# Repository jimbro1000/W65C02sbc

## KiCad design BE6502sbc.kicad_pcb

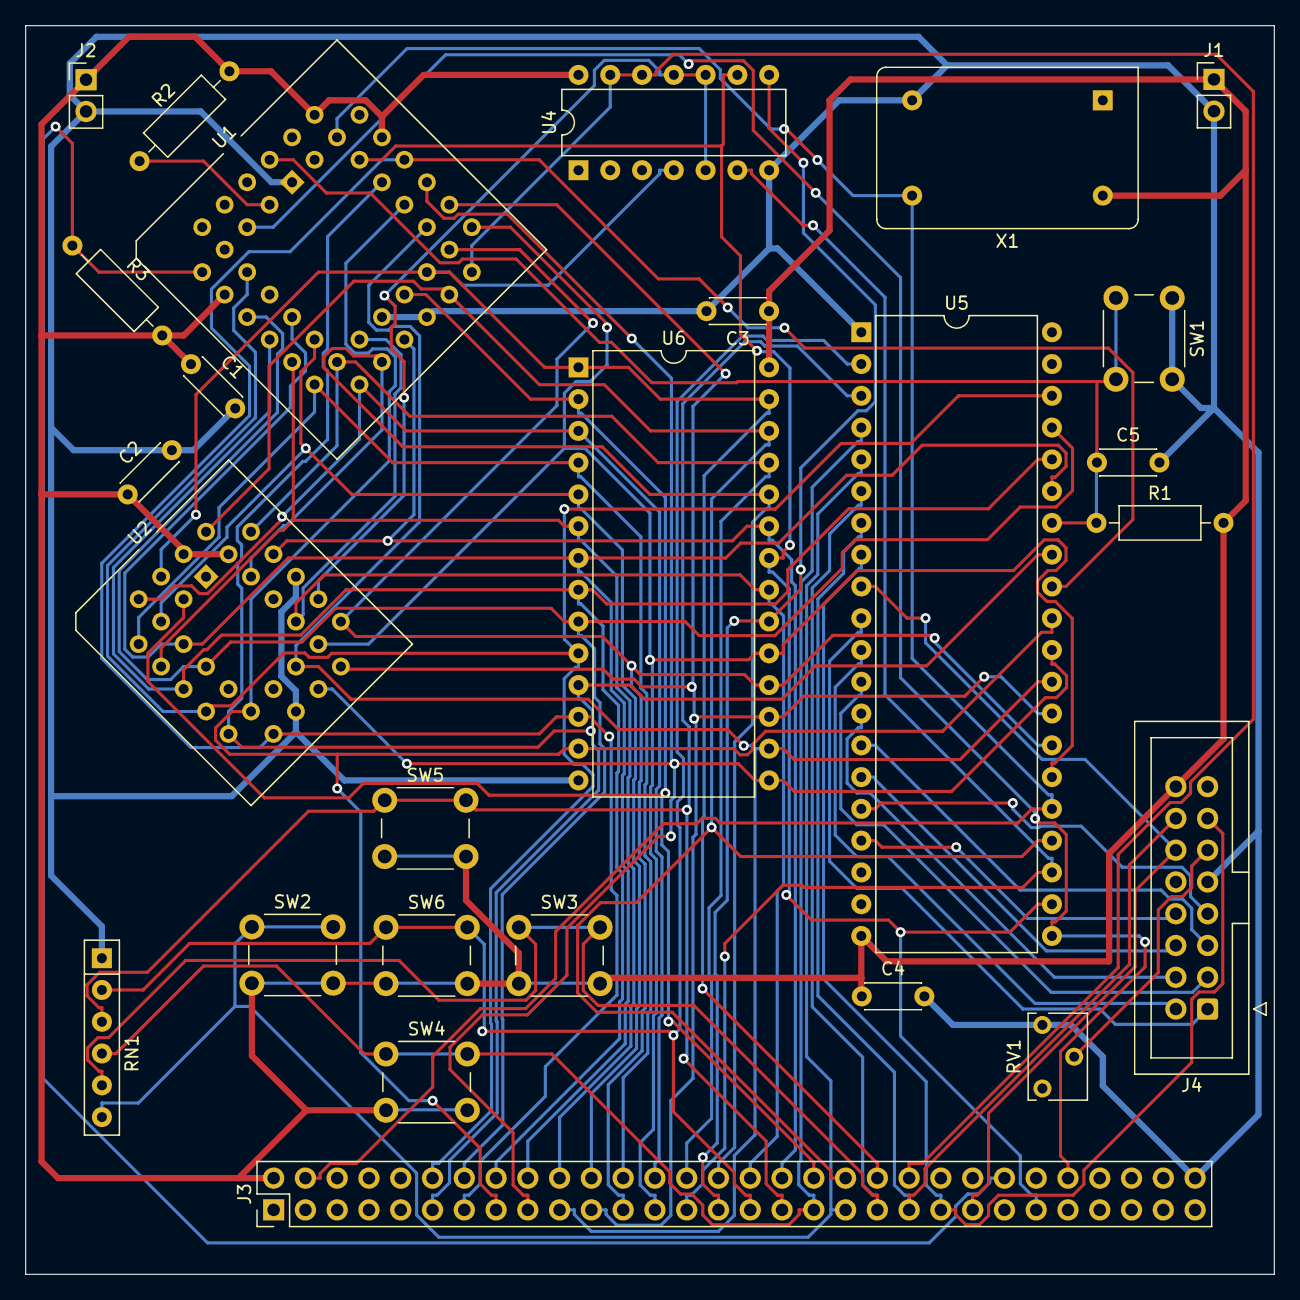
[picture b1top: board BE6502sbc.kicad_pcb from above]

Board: 2 copper layers, 99.8 x 99.8 mm, 26 parts (0 on the bottom side), 52 nets.

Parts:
C1, C2, C3, C4, C5: 100nF; C_Disc_D4.3mm_W1.9mm_P5.00mm
J1, J2: power; PinHeader_1x02_P2.54mm_Vertical
J3: Conn_02x30_Odd_Even; PinHeader_2x30_P2.54mm_Vertical
J4: LCD_DISPLAY; IDC-Header_2x08_P2.54mm_Vertical
R1, R2, R3: 1K; R_Axial_DIN0207_L6.3mm_D2.5mm_P10.16mm_Horizontal
RN1: 1K; R_Array_SIP6
RV1: 10K; Potentiometer_Bourns_3266W_Vertical
SW1: RESET; SW_PUSH_6mm
SW2: LEFT; SW_PUSH_6mm
SW3: RIGHT; SW_PUSH_6mm
SW4: DOWN; SW_PUSH_6mm
SW5: UP; SW_PUSH_6mm
SW6: SELECT; SW_PUSH_6mm
U1: W65C02; PLCC-44_THT-Socket
U2: 28C256; PLCC-32_THT-Socket
U4: 74HC00; DIP-14_W7.62mm
U5: 6522; DIP-40_W15.24mm
U6: KM62256CLP; DIP-28_W15.24mm
X1: 1MHz; Oscillator_DIP-14

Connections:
+5V: C1.1, C2.1, C3.1, C4.1, J1.1, J2.1, J3.2, J4.16, R1.2, R2.2, R3.2, SW2.2 (B), SW3.2 (B), SW4.2 (B), SW5.2 (B), SW6.2 (B), U1.9 (VCC), U1.37 (VCC), U1.40 (BE), U2.31 (~WE), U2.32 (VCC), U4.14 (VCC), U5.20 (VCC), U6.28 (VCC), X1.14 (Vcc)
A0: J3.12, U1.10 (A0), U2.11 (A0), U5.38 (RS0), U6.10 (A0)
A1: J3.14, U1.11 (A1), U2.10 (A1), U5.37 (RS1), U6.9 (A1)
A2: J3.16, U1.13 (A2), U2.9 (A2), U5.36 (RS2), U6.8 (A2)
A3: J3.18, U1.14 (A3), U2.8 (A3), U5.35 (RS3), U6.7 (A3)
A4: J3.20, U1.15 (A4), U2.7 (A4), U6.6 (A4)
A5: J3.22, U1.16 (A5), U2.6 (A5), U6.5 (A5)
A6: J3.24, U1.17 (A6), U2.5 (A6), U6.4 (A6)
A7: J3.26, U1.18 (A7), U2.4 (A7), U6.3 (A7)
A8: J3.28, U1.19 (A8), U2.29 (A8), U6.25 (A8)
A9: J3.30, U1.20 (A9), U2.28 (A9), U6.24 (A9)
A10: J3.32, U1.21 (A10), U2.24 (A10), U6.21 (A10)
A11: J3.34, U1.22 (A11), U2.27 (A11), U6.23 (A11)
A12: J3.36, U1.25 (A12), U2.3 (A12), U6.2 (A12)
A13: J3.38, U1.26 (A13), U2.30 (A13), U5.24 (CS1), U6.26 (A13)
A14: J3.40, U1.27 (A14), U2.2 (A14), U4.4, U6.1 (A14), U6.27 (~WE)
A15: J3.42, U1.28 (A15), U4.12, U4.13
BACKLIGHT: J4.11, RV1.2
CLK: J3.4, U1.41 (PHI2), U5.25 (PHI2), X1.8 (OUT)
D0: J3.11, U1.36 (D0), U2.13 (D0), U5.33 (D0), U6.11 (Q0)
D1: J3.13, U1.35 (D1), U2.14 (D1), U5.32 (D1), U6.12 (Q1)
D2: J3.15, U1.34 (D2), U2.15 (D2), U5.31 (D2), U6.13 (Q2)
D3: J3.17, U1.33 (D3), U2.18 (D3), U5.30 (D3), U6.15 (Q3)
D4: J3.19, U1.32 (D4), U2.19 (D4), U5.29 (D4), U6.16 (Q4)
D5: J3.21, U1.31 (D5), U2.20 (D5), U5.28 (D5), U6.17 (Q5)
D6: J3.23, U1.30 (D6), U2.21 (D6), U5.27 (D6), U6.18 (Q6)
D7: J3.25, U1.29 (D7), U2.22 (D7), U5.26 (D7), U6.19 (Q7)
GND: C1.2, C2.2, C3.2, C4.2, C5.2, J1.2, J2.2, J3.60, J4.9, RN1.1 (common), RV1.1, SW1.1 (A), U1.1 (GND), U1.23 (GND), U1.24 (GND), U2.16 (GND), U2.25 (~OE), U4.7 (GND), U5.1 (GND), U6.14 (GND), X1.7 (GND)
LCD_DB0: J4.1, U5.10 (PB0)
LCD_DB1: J4.2, U5.11 (PB1)
LCD_DB2: J4.3, U5.12 (PB2)
LCD_DB3: J4.4, U5.13 (PB3)
LCD_DB4: J4.5, U5.14 (PB4)
LCD_DB5: J4.6, U5.15 (PB5)
LCD_DB6: J4.7, U5.16 (PB6)
LCD_DB7: J4.8, U5.17 (PB7)
LCD_E: J3.45, J4.12, U5.9 (PA7)
LCD_RS: J3.41, J4.14, U5.7 (PA5)
LCD_R/W: J3.43, J4.13, U5.8 (PA6)
MEM-SELECT: J3.29, U4.8, U6.20 (~CS)
unnamed: R2.1, U1.3 (RDY)
ROM-SELECT: U2.23 (~CS), U4.5, U4.10, U4.11
R/~W: J3.49, U1.38 (R/~W), U4.9, U5.22 (R/~W), U6.22 (~OE)
SW_DOWN: J3.35, RN1.4 (R3), SW4.1 (A), U5.4 (PA2)
SW_LEFT: J3.37, RN1.6 (R5), SW2.1 (A), U5.5 (PA3)
SW_RIGHT: J3.39, RN1.5 (R4), SW3.1 (A), U5.6 (PA4)
SW_SEL: J3.31, RN1.2 (R1), SW6.1 (A), U5.2 (PA0)
SW_UP: J3.33, RN1.3 (R2), SW5.1 (A), U5.3 (PA1)
VIA-SELECT: J3.27, U4.6, U5.23 (~CS2)
~IRQ: J3.52, U1.5 (~IRQ), U5.21 (~IRQ)
~NMI: J3.48, R3.1, U1.7 (~NMI)
~RST: C5.1, R1.1, SW1.2 (B), U1.44 (~RESET), U5.34 (~RESET)
